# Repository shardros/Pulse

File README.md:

# Tracer
Computer Science Coursework

At somepoint there will hopefully be software he to perform autorouting of PCB's

## Notes
http://plantuml.com/

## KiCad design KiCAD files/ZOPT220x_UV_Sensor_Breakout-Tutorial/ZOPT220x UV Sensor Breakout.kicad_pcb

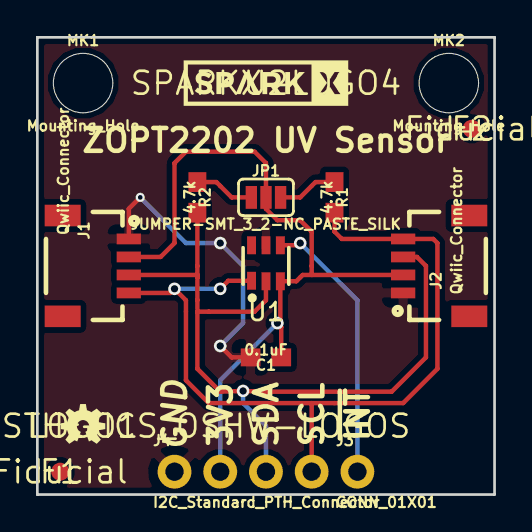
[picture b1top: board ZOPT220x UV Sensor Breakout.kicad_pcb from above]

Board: 2 copper layers, 25.4 x 25.4 mm, 17 parts (1 on the bottom side), 7 nets.

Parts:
C1: 0.1uF; 0603
F1, F2: Fiducial; FIDUCIAL-1X2
J1, J2: Qwiic_Connector; 1X04_1MM_RA
J3: CONN_01X01; 1X01_NO_SILK
J4: I2C_Standard_PTH_Connector; 1X04_NO_SILK
JP1: JUMPER-SMT_3_2-NC_PASTE_SILK; SMT-JUMPER_3_2-NC_PASTE_SILK
LOGO1: SPARKFUN-AESTHETICS_OSHW-LOGOS; OSHW-LOGO-MINI
MK1, MK2: Mounting_Hole; STAND-OFF
R1, R2: 4.7k; 0603
U1: ZOPT220X; ZOPT220x
U2, U3: SPARKX-LOGO4; SPARKX-MEDIUM
U4: CC_LICENSE; CREATIVE_COMMONS

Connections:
+3V3: C1.1, J1.2, J2.2, J4.2, JP1.2, U1.3
GND: C1.2, J1.1, J2.1, J4.1, U1.5
unnamed: JP1.1, R2.1
unnamed: JP1.3, R1.1
SCL: J1.4, J2.4, J4.4, R1.2, U1.1
SDA: J1.3, J2.3, J4.3, R2.2, U1.2
~INT: J3.1, U1.4

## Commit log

2018-10-14 Added KiCAD files
2018-10-14 Added Net and PCB Classes
2018-10-14 Wave propogation to find a point from another
2018-10-14 Refactored to be nice
2018-10-14 Amended comment
2018-10-14 Make the array size sensible
2018-10-14 Reformat to remove lazy evaluation problems
2018-10-16 Compeleted route back
2018-10-16 Create classes
2018-10-17 Created NetRouter and BoardRouter Classes
2018-10-17 remove space
2018-10-17 Copy Valid to add over to app.js
    Create methods inside app.js board router
2018-10-19 OOP single net routing
2018-10-19 Clean up the logs
2018-11-17 Added writeup doc
2018-11-18 add prototyping and research
2018-11-21 Added research into alogrithiums and "citations"
2018-11-22 Updates to .gitignore
2018-11-22 Finalize project section of analysis
2018-11-23 Finalized analysis
2018-12-04 Added support for no go area's
2018-12-06 Cleaned up output of NetRouter function
2018-12-10 SubClassed NetRouter into BoardRouter
2018-12-18 Rename to grid propergate
2018-12-18 Node dependancies
2018-12-18 References for better routers
2018-12-19 Split up into modules
    Added priority queue class and started work on router class
2018-12-19 Start adding priority queue
2018-12-20 Added enqueue method to priority queue
2018-12-20 Kinda got dequeue working
2018-12-22 Added import statemetns
2018-12-22 Propper intergration between modules
2018-12-27 Mostly working A Star router
2018-12-27 Update Node modules
2018-12-27 huristic -> heuristic
2018-12-29 Dependancies
2018-12-29 Netrouter sensible output
2018-12-29 Revert "Dependancies"
    This reverts commit 213fa111525ca412867da6d855254d4d8b0f6664.
2019-01-11 Moving to electron
2019-01-11 Node modules
2019-01-11 Update folder strucutre
2019-01-13 Update read me
2019-01-13 Added notes on HR Proxy Cert to readme
2019-01-13 Added basic JS module for creating svg's
2019-01-13 Added file handeling to SVG module
2019-01-15 Clean up of node modules
2019-01-15 tidy up of the repo
2019-01-15 Update gitignore
2019-01-15 Class refacting for proper use of modules
2019-01-15 Made the SVG finally work
2019-01-16 Create LICENSE
2019-01-16 test
2019-01-16 Improved svg class
2019-01-16 Can now route multiple nets
2019-01-18 Fix neighbours not being marked as non-routeable
2019-01-18 Added comments to router.js
2019-01-19 Fixxed acessing cells not on board
2019-01-20 Added comments
2019-01-20 Started to add front end
2019-01-20 Canvas now works
2019-01-20 Improvements to front end
2019-01-21 Added keep out functionality
2019-01-21 Flood that floods everything
2019-01-22 Fixxed routes and floods being too close, diagonals enabled
2019-01-22 Flooding renabled
2019-01-22 Added more routes for self-esteem
2019-01-22 Non crashing default config
2019-01-23 Added moving rectangle on mouse move
2019-01-23 Added useful websever for servering many files
2019-01-23 Moved to module based imports
2019-01-24 Added support for multiple end points
2019-01-25 Started move to ultra thin AJAX client
2019-01-25 Added comments and JSDOC everywhere
2019-01-25 Added basic AJAX comunication
2019-01-25 Send JSON in body
2019-01-25 Convert requested data into request object
2019-01-26 Client now recives SVG data back based on request
2019-01-26 Added return functionality to async update
2019-01-27 Support for client specified parameters of SVG
2019-01-27 Restructure of the cell class
    The Cell class now contains all of the movement functions
2019-01-29 Net now moves on drag :-)
2019-01-29 Got many routes at once working with auto drag
2019-01-29 Added error catching
2019-02-01 Fixed catch
2019-02-01 Working board router
2019-02-01 Got CSS grid working
2019-02-01 SVG resized correctly
2019-02-03 Migrated net to fit within resized pannel
2019-02-03 Programatically create nets
2019-02-03 Move script out of HTML
2019-02-03 HANDSSS!!!
2019-02-04 Fixxed positioning of the cells
2019-02-04 Colour update
2019-02-04 Updated manhattan distance to be the correct dist
2019-02-05 Formating
2019-02-05 Not really sure
2019-02-05 Fix shorting bug
2019-02-05 Fixxed lodash vunrability
2019-02-05 Fixxed rendering
2019-02-06 Ignore board sections
2019-02-08 Fixed shorts
2019-02-10 Flooding added
2019-02-10 Got deleting working
2019-02-11 Priority routing
2019-02-11 Error handeling
2019-02-11 Added hardrouteable methods to board class
2019-02-11 Overiding stable
2019-02-12 Fixxed server side hard routing issues
2019-02-12 Cells now can't be placed in the same location
2019-02-12 Added not being able to get too close to another node
2019-02-14 Stability improvements
2019-02-14 Package JSON updates
2019-02-15 Fixxed move by one bug
2019-02-15 Can't remeber
2019-02-15 Thing
2019-02-17 Fixxed netRouter not understanding checked
2019-02-22 Better board router error handeling, has BUGS
2019-02-22 Error handeling for out of bounds senarios
2019-02-24 End product
2019-02-25 Write up
2019-02-25 Writeup
2019-02-25 Writeup technical solution
2019-02-26 Spelling
2019-02-28 Comments and formating
2019-03-12 Update writeup
2019-03-12 Finnal version of writeup

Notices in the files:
parts and their libraries:
Released under the Creative Commons Attribution Share-Alike 4.0 License
https://creativecommons.org/licenses/by-sa/4.0
